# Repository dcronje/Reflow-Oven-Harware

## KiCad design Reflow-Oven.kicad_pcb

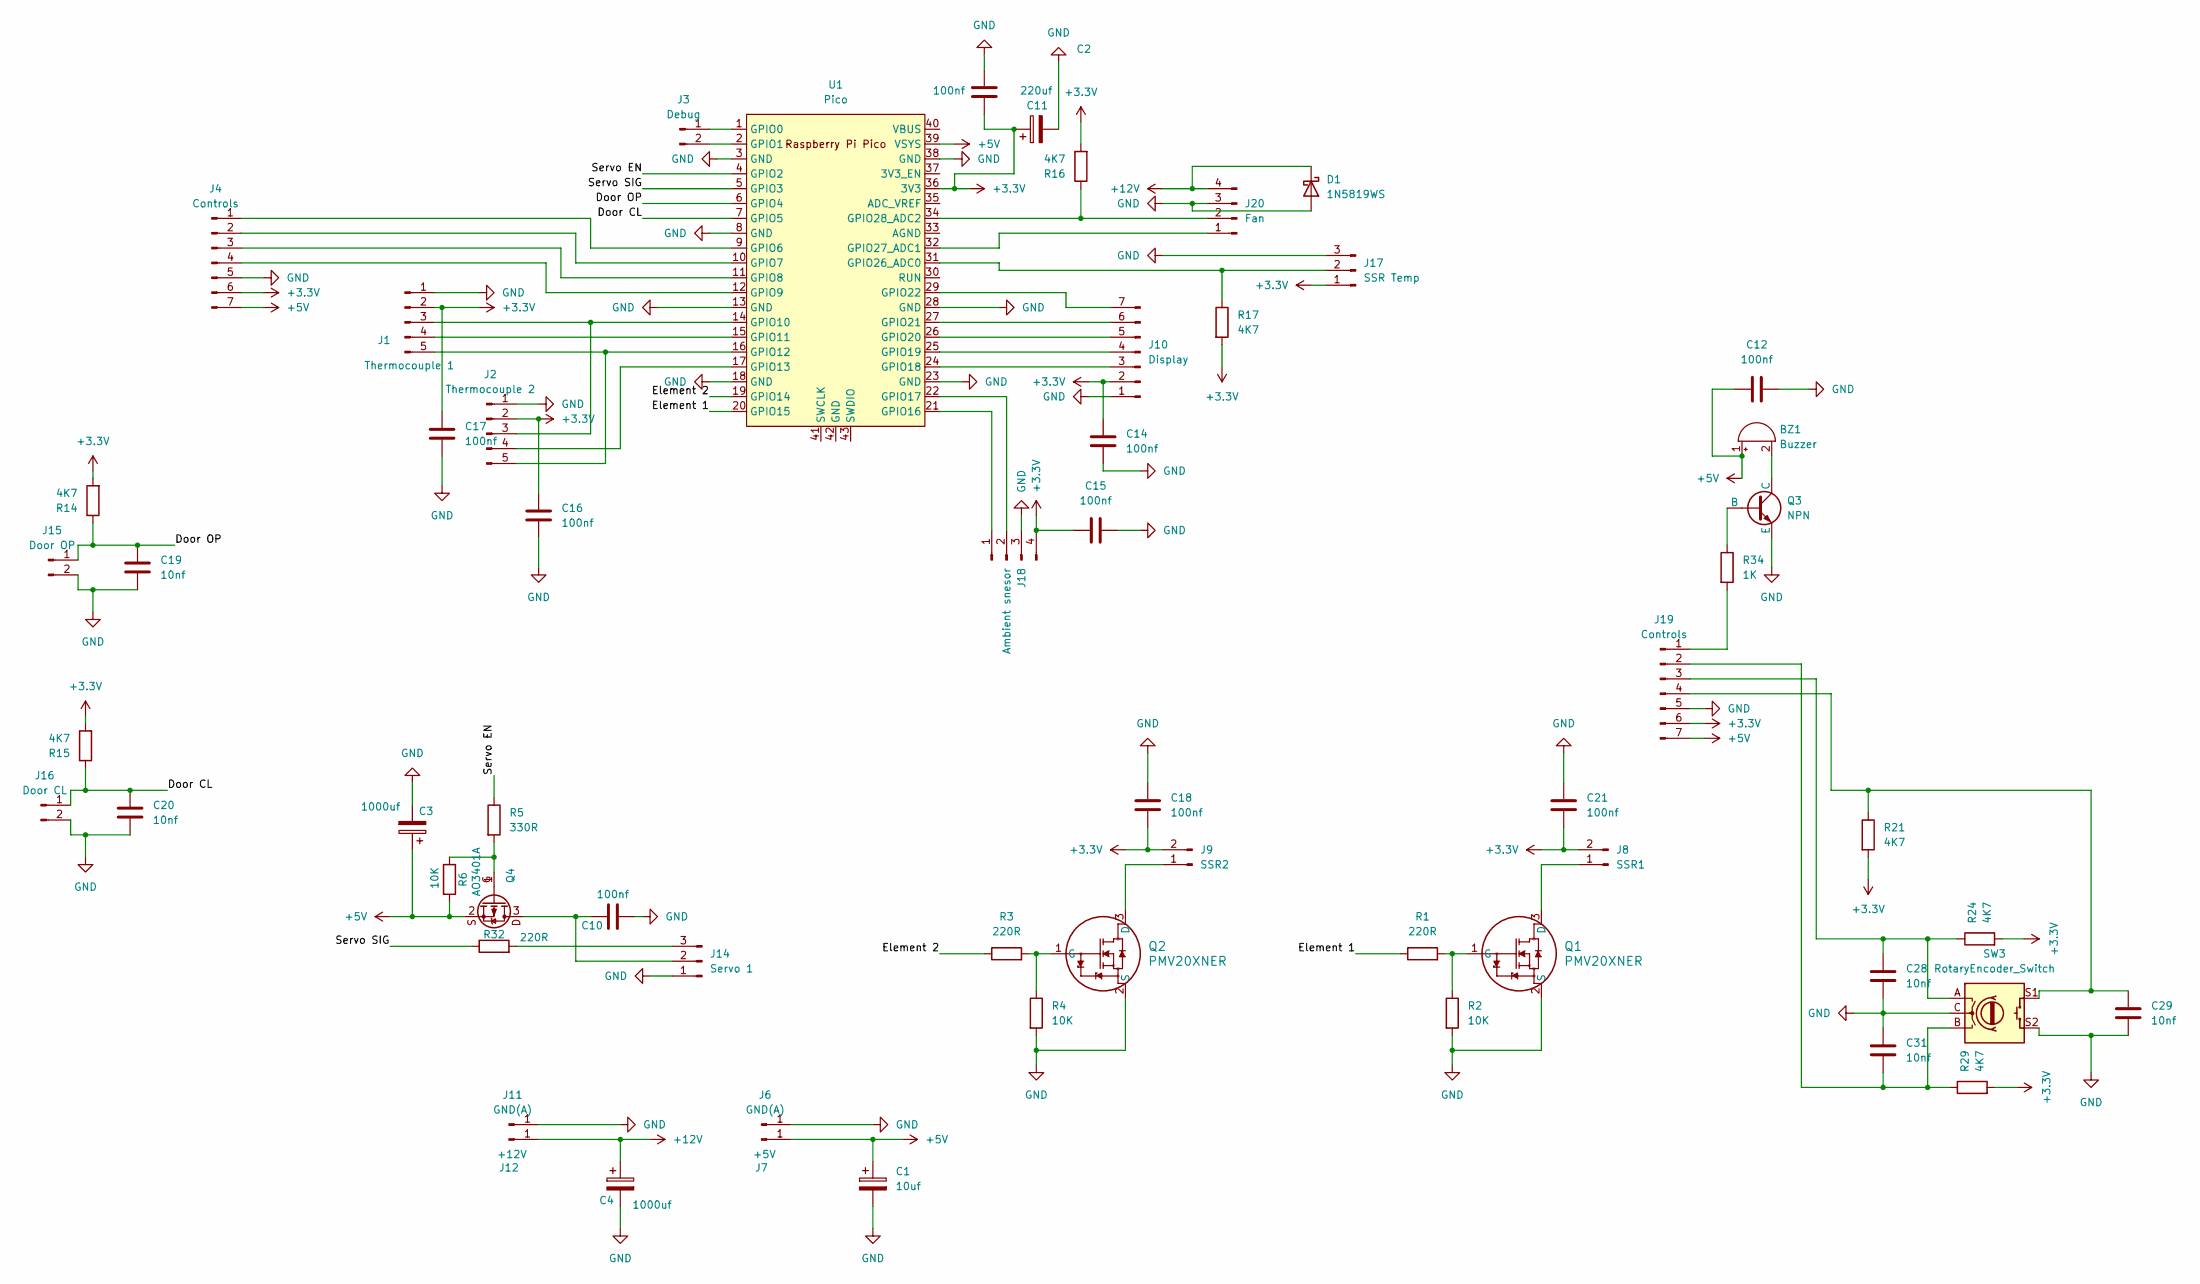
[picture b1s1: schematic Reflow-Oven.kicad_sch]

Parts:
BZ1: Buzzer; Buzzer_Mallory_AST1109MLTRQ
C1: 10uf; CP_Elec_4x5.4
C2: 220uf; CP_Elec_8x10.5
C3, C4: 1000uf; CP_Elec_10x10.5
C10, C11, C12, C14, C15, C16, C17, C18, C21: 100nf; C_1210_3225Metric_Pad1.33x2.70mm_HandSolder
C19, C20, C28, C29, C31: 10nf; C_1206_3216Metric_Pad1.33x1.80mm_HandSolder
D1: 1N5819WS; D_SOD-323_HandSoldering
J1: Thermocouple 1; PinHeader_1x05_P2.54mm_Vertical_SMD
J2: Thermocouple 2; PinHeader_1x05_P2.54mm_Vertical_SMD
J3: Debug; PinHeader_1x02_P2.54mm_Vertical_SMD
J4: Controls; PinHeader_1x07_P2.54mm_Vertical_SMD
J6, J11: GND(A); SolderWirePad_1x01_SMD_5x10mm
J7: +5V; SolderWirePad_1x01_SMD_5x10mm
J8: SSR1; PinHeader_1x02_P2.54mm_Vertical_SMD
J9: SSR2; PinHeader_1x02_P2.54mm_Vertical_SMD
J10: Display; PinHeader_1x07_P2.54mm_Vertical_SMD
J12: +12V; SolderWirePad_1x01_SMD_5x10mm
J14: Servo 1; PinHeader_1x03_P2.54mm_Vertical_SMD
J15: Door OP; PinHeader_1x02_P2.54mm_Vertical_SMD
J16: Door CL; PinHeader_1x02_P2.54mm_Vertical_SMD
J17: SSR Temp; PinHeader_1x03_P2.54mm_Vertical_SMD
J18: Ambient snesor; PinHeader_1x04_P2.54mm_Vertical_SMD
J19: Controls; PinHeader_1x07_P2.54mm_Vertical
J20: Fan; PinHeader_1x04_P2.54mm_Vertical_SMD
Q1, Q2: PMV20XNER; SOT23-TO-236AB_NEX
Q3: NPN; TSOT-23
Q4: AO3401A; SOT23-TO-236AB_NEX
R1, R3, R32: 220R; R_1206_3216Metric
R2, R4, R6: 10K; R_1206_3216Metric
R5: 330R; R_1206_3216Metric
R14, R15, R16, R17, R21, R24, R29: 4K7; R_1206_3216Metric
R34: 1K; R_1206_3216Metric
SW3: RotaryEncoder_Switch; RotaryEncoder_Alps_EC11E-Switch_Vertical_H20mm_SMD
U1: Pico; RPi_Pico_SMD

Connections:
+3.3V: C2.1, C11.1, C14.2, C15.2, C16.2, C17.1, C18.1, C21.1, J1.2, J2.2, J4.6, J8.2, J9.2, J10.2, J17.1, J18.4, J19.6, R14.2, R15.2, R16.2, R17.2, R21.2, R24.2, R29.2, U1.36 (3V3)
+5V: BZ1.1 (+), C1.1, C3.1, C12.1, J4.7, J7.1, J19.7, Q4.2 (S), R6.2, U1.39 (VSYS)
+12V: C4.1, D1.1 (K), J12.1, J20.4
/Door CL: C20.2, J16.1, R15.1, U1.7 (GPIO5)
/Door OP: C19.2, J15.1, R14.1, U1.6 (GPIO4)
/Element 1: R1.1, U1.20 (GPIO15)
/Element 2: R3.1, U1.19 (GPIO14)
/Servo EN: R5.1, U1.4 (GPIO2)
/Servo SIG: R32.1, U1.5 (GPIO3)
GND: C1.2, C2.2, C3.2, C4.2, C10.2, C11.2, C12.2, C14.1, C15.1, C16.1, C17.2, C18.2, C19.1, C20.1, C21.2, C28.1, C29.2, C31.2, D1.2 (A), J1.1, J2.1, J4.5, J6.1, J10.1, J11.1, J14.1, J15.2, J16.2, J17.3, J18.3, J19.5, J20.3, Q1.2 (S), Q2.2 (S), Q3.3 (E), R2.2, R4.2, SW3.C, SW3.S2, U1.3 (GND), U1.8 (GND), U1.13 (GND), U1.18 (GND), U1.23 (GND), U1.28 (GND), U1.38 (GND)
unnamed: BZ1.2 (-), Q3.1 (C)
unnamed: J1.3, J2.3, U1.14 (GPIO10)
unnamed: J1.4, U1.15 (GPIO11)
unnamed: J1.5, J2.5, U1.16 (GPIO12)
unnamed: J2.4, U1.17 (GPIO13)
unnamed: J3.1, U1.1 (GPIO0)
unnamed: J3.2, U1.2 (GPIO1)
unnamed: J4.1, U1.9 (GPIO6)
unnamed: J4.2, U1.10 (GPIO7)
unnamed: J4.3, U1.11 (GPIO8)
unnamed: J4.4, U1.12 (GPIO9)
unnamed: J8.1, Q1.3 (D)
unnamed: J9.1, Q2.3 (D)
unnamed: J10.3, U1.24 (GPIO18)
unnamed: J10.4, U1.25 (GPIO19)
unnamed: J10.5, U1.26 (GPIO20)
unnamed: J10.6, U1.27 (GPIO21)
unnamed: J10.7, U1.29 (GPIO22)
unnamed: C10.1, J14.2, Q4.3 (D)
unnamed: J14.3, R32.2
unnamed: J17.2, R17.1, U1.31 (GPIO26_ADC0)
unnamed: J18.1, U1.21 (GPIO16)
unnamed: J18.2, U1.22 (GPIO17)
unnamed: J19.1, R34.2
unnamed: C31.1, J19.2, R29.1, SW3.B
unnamed: C28.2, J19.3, R24.1, SW3.A
unnamed: C29.1, J19.4, R21.1, SW3.S1
unnamed: J20.1, U1.32 (GPIO27_ADC1)
unnamed: J20.2, R16.1, U1.34 (GPIO28_ADC2)
unnamed: Q1.1 (G), R1.2, R2.1
unnamed: Q2.1 (G), R3.2, R4.1
unnamed: Q3.2 (B), R34.1
unnamed: Q4.1 (G), R5.2, R6.1

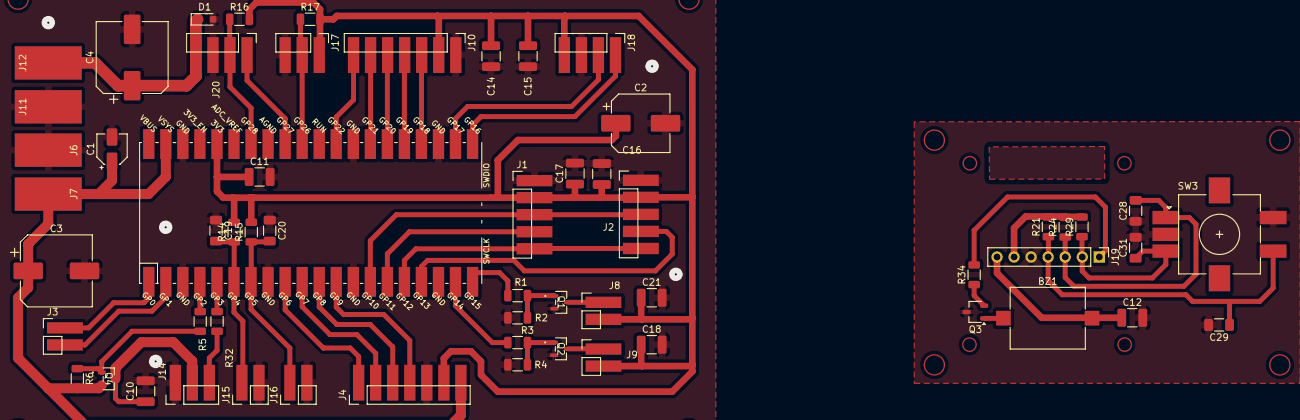
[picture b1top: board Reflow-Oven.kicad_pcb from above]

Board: 2 copper layers, 59 parts (0 on the bottom side), 43 nets.

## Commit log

2025-04-21 Initial
2025-04-22 Single servo with cutoff
